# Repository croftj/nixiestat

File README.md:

# NixieStat Home Thermostat

NxieStat is thermostat for the home with a nixie tube display supporting
remote sensors.

All comminications to the thermostat is over wifi using the Mosquitto MQTT
message bus. The messages are in the form of json strings. 

This prject started out as an AVR based thermostat. You will see vestiges of
that in source tree. The latest code and hardware is under the **esp32**
folder. The hope is that there will be a web ui running on a Raspberry PI. The
start of this code is in the **webui** folder. It is very early code that is
mostly to prove certain components/SDKs such as **QT** & **WT** can actually be 
compiled together on the Rasberry PI.

## Hardware

### Devboard
This is currently the most tested of the two ESP32 boards. It handle an
ESP32-S2 processor. It also has a three pin connector for easily attaching a
DS18S20 temperature sensor to it. Its  primary purpose is for the temperature
sensors.

### Devboard2
This board is similar to *DevBoard* except that it is laid out for the
ESP32-WROVER-IE processor. This board has not been tested yet. It will
hopefully be the processor for use as the thermostat itself and be able to be
upgraded *over the air*

### CPU Board
This board has the relays for the furnace as wll as the interface chips for the
keyboard an the display board. It can use either *Devboard* or *Devboard2* for
it's processor board.

## Nixie Display
This board has the High voltage supply as well as the nixie tubes and neon
bulbs for the display.

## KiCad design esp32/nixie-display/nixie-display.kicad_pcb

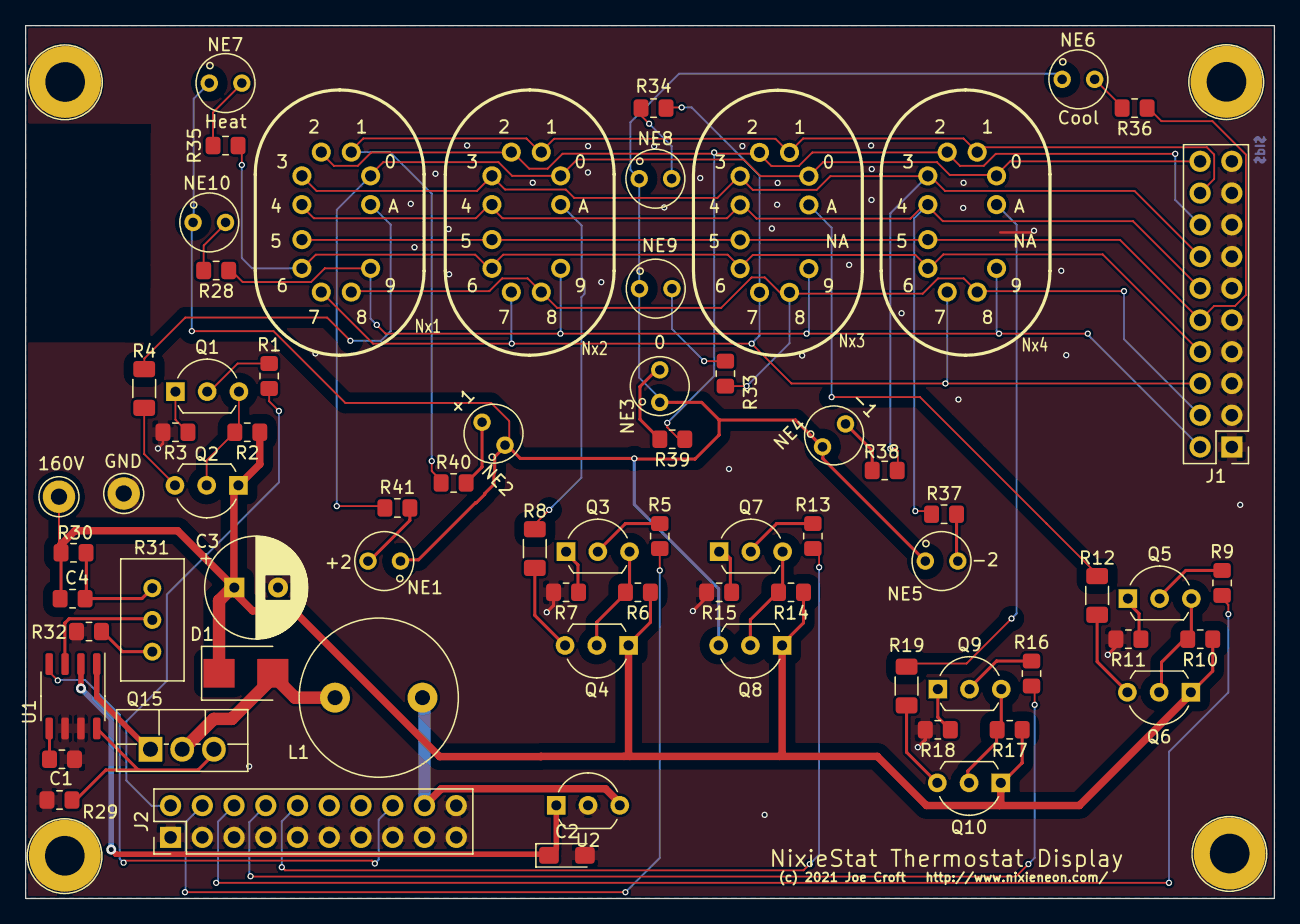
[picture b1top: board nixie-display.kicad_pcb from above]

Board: 2 copper layers, 99.9 x 69.8 mm, 74 parts (0 on the bottom side), 61 nets.

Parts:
C1: 1nf; R_0805_2012Metric_Pad1.20x1.40mm_HandSolder
C2: 10uf; CP_EIA-3216-18_Kemet-A_Pad1.58x1.35mm_HandSolder
C3: 4.7uf; CP_Radial_D8.0mm_P3.50mm
C4: 2.2nf; R_0805_2012Metric_Pad1.20x1.40mm_HandSolder
D1: D_Schottky; D_SMB
J1, J2: Conn_02x10_Odd_Even; PinHeader_2x10_P2.54mm_Vertical
L1: 150uh; L_Radial_D12.5mm_P7.00mm_Fastron_09HCP
NE1: +2; NE2
NE2: +1; NE2
NE3: 0; NE2
NE4: -1; NE2
NE5: -2; NE2
NE6: Cool; NE2
NE7: Heat; NE2
NE8, NE9, NE10: Lamp_Neon; NE2
Nx1, Nx2, Nx3, Nx4: in17
Q1, Q3, Q5, Q7, Q9: MPSA42; TO-92L_Inline_Wide
Q2, Q4, Q6, Q8, Q10: MPSA92; TO-92L_Inline_Wide
Q15: IRLS640; TO-220F-3_Vertical
R1, R3, R5, R7, R9, R11, R13, R15, R16, R18: 3.3K; R_0805_2012Metric_Pad1.20x1.40mm_HandSolder
R2, R6, R10, R14, R17, R28, R33, R34, R35, R36, R37, R38, R39, R40, R41: 100K; R_0805_2012Metric_Pad1.20x1.40mm_HandSolder
R4, R8, R12, R19: 22K; R_1206_3216Metric_Pad1.30x1.75mm_HandSolder
R29: .1; R_0805_2012Metric_Pad1.20x1.40mm_HandSolder
R30: 1M; R_0805_2012Metric_Pad1.20x1.40mm_HandSolder
R31: 20K; Potentiometer_Bourns_3296W_Vertical
R32: 1.2K; R_0805_2012Metric_Pad1.20x1.40mm_HandSolder
SH1, SH2, SH3, SH4: ScrewHole; 4-40-Screw
TP1: 160V; Pin_D1.3mm_L11.0mm
TP2: GND; Pin_D1.3mm_L11.0mm
U1: MAX1771; SO-8_3.9x4.9mm_P1.27mm
U2: L78L05_TO92; TO-92_Inline_Wide

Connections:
160V: C3.1, C4.1, D1.1, Q2.1, Q4.1, Q6.1, Q8.1, Q10.1, R2.1, R6.1, R10.1, R14.1, R17.1, R30.1, TP1.1
+5V: C2.1, U1.2, U2.1
/seg0: J1.20, Nx1.0, Nx2.0, Nx3.0, Nx4.0, R41.1
/seg1: J1.18, Nx1.1, Nx2.1, Nx3.1, Nx4.1, R40.1
/seg2: J1.16, Nx1.2, Nx2.2, Nx3.2, Nx4.2, R39.1
/seg3: J1.14, Nx1.3, Nx2.3, Nx3.3, Nx4.3, R38.1
/seg4: J1.12, Nx1.4, Nx2.4, Nx3.4, Nx4.4, R37.1
/seg5: J1.10, Nx1.5, Nx2.5, Nx3.5, Nx4.5, R36.1
/seg6: J1.8, Nx1.6, Nx2.6, Nx3.6, Nx4.6, R35.1
/seg7: J1.6, Nx1.7, Nx2.7, Nx3.7, Nx4.7, R34.1
/seg8: J1.4, Nx1.8, Nx2.8, Nx3.8, Nx4.8, R33.1
/seg9: J1.2, Nx1.9, Nx2.9, Nx3.9, Nx4.9, R28.1
GNDREF: C1.2, C2.2, C3.2, J1.1, J1.3, J1.5, J1.7, J1.9, J1.11, J1.13, J1.15, J1.17, J1.19, J2.1, J2.3, J2.5, J2.7, J2.9, J2.11, J2.13, J2.15, J2.17, J2.19, J2.20, R3.2, R7.2, R11.2, R15.2, R18.2, R29.2, R32.2, SH1.1, SH2.1, SH3.1, SH4.1, TP2.1, U1.6, U1.7, U2.2
HV_DISABLE: J2.16, U1.4
unnamed: C1.1, U1.5
unnamed: C4.2, R30.2, R31.1
unnamed: D1.2, L1.2, Q15.2
unnamed: NE1.2, R41.2
unnamed: NE2.2, R40.2
unnamed: NE3.2, R39.2
unnamed: NE4.2, R38.2
unnamed: NE5.2, R37.2
unnamed: NE6.2, R36.2
unnamed: NE7.2, R35.2
unnamed: NE8.2, R34.2
unnamed: NE9.2, R33.2
unnamed: NE10.2, R28.2
unnamed: Q1.1, R3.1
unnamed: Q1.2, R1.1
unnamed: Q1.3, Q2.2, R2.2
unnamed: Q2.3, R4.2
unnamed: Q3.1, R7.1
unnamed: Q3.2, R5.1
unnamed: Q3.3, Q4.2, R6.2
unnamed: Q4.3, R8.2
unnamed: Q5.1, R11.1
unnamed: Q5.2, R9.1
unnamed: Q5.3, Q6.2, R10.2
unnamed: Q6.3, R12.2
unnamed: Q7.1, R15.1
unnamed: Q7.2, R13.1
unnamed: Q7.3, Q8.2, R14.2
unnamed: Q9.1, R18.1
unnamed: Q9.2, R16.1
unnamed: Q9.3, Q10.2, R17.2
unnamed: Q10.3, R19.2
unnamed: Q15.1, U1.1
unnamed: Q15.3, R29.1, U1.8
unnamed: R31.2, U1.3
unnamed: R31.3, R32.1
VCC: J2.18, L1.1, U2.3
dig0: Nx1.A, R4.1
dig1: Nx2.A, R8.1
dig2: Nx3.A, R12.1
dig3: Nx4.A, R19.1
dig4: NE1.1, NE2.1, NE3.1, NE4.1, NE5.1, NE6.1, NE7.1, NE8.1, NE9.1, NE10.1, Q8.3
idig0: J2.2, R1.2
idig1: J2.4, R5.2
idig2: J2.6, R9.2
idig3: J2.8, R16.2
idig4: J2.10, R13.2

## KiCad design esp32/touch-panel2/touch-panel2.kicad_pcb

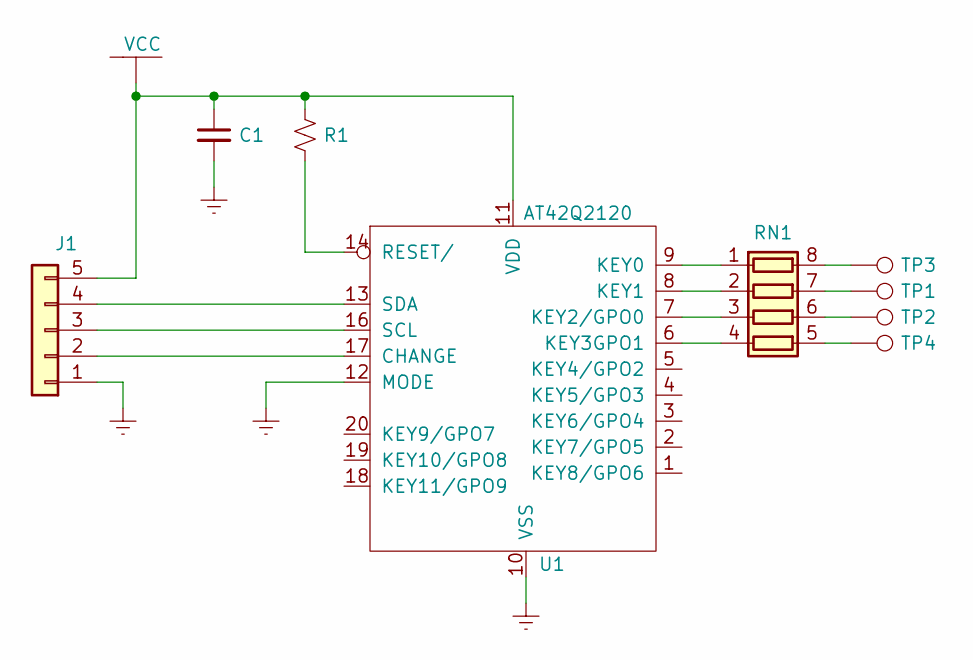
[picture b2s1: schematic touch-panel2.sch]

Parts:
C1: C_Small; C_0805_2012Metric_Pad1.18x1.45mm_HandSolder
J1: Conn_01x05; PinHeader_1x05_P2.54mm_Vertical
R1: R_Small_US; R_0805_2012Metric_Pad1.20x1.40mm_HandSolder
RN1: R_Pack04; R_Array_Convex_4x0603
TP1, TP2, TP3, TP4: TestPoint; Touch_Pad_Small
U1: AT42Q2120; TSSOP-20_4.4x6.5mm_P0.65mm
V1: VCC

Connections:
GNDREF: C1.2, J1.1, U1.10 (VSS), U1.12 (MODE)
unnamed: J1.2, U1.17 (CHANGE)
unnamed: J1.3, U1.16 (SCL)
unnamed: J1.4, U1.13 (SDA)
unnamed: R1.2, U1.14 (RESET/)
unnamed: RN1.1 (R1.1), U1.9 (KEY0)
unnamed: RN1.2 (R2.1), U1.8 (KEY1)
unnamed: RN1.3 (R3.1), U1.7 (KEY2/GPO0)
unnamed: RN1.4 (R4.1), U1.6 (KEY3GPO1)
unnamed: RN1.5 (R4.2), TP4.1
unnamed: RN1.6 (R3.2), TP2.1
unnamed: RN1.7 (R2.2), TP1.1
unnamed: RN1.8 (R1.2), TP3.1
VCC: C1.1, J1.5, R1.1, U1.11 (VDD), V1.1

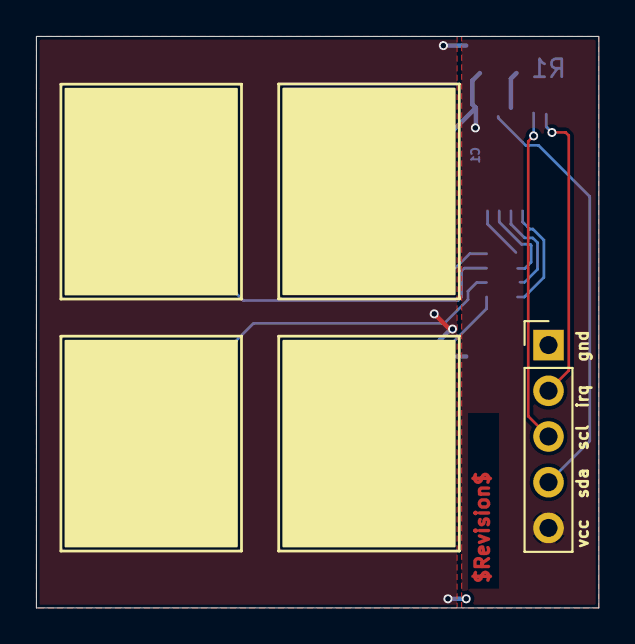
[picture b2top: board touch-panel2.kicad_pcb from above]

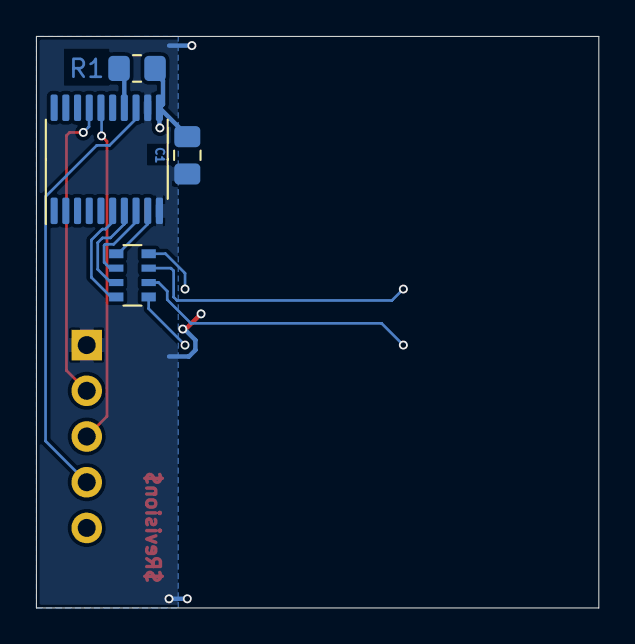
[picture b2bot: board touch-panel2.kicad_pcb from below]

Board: 2 copper layers, 31.2 x 31.7 mm, 9 parts (4 on the bottom side), 14 nets.

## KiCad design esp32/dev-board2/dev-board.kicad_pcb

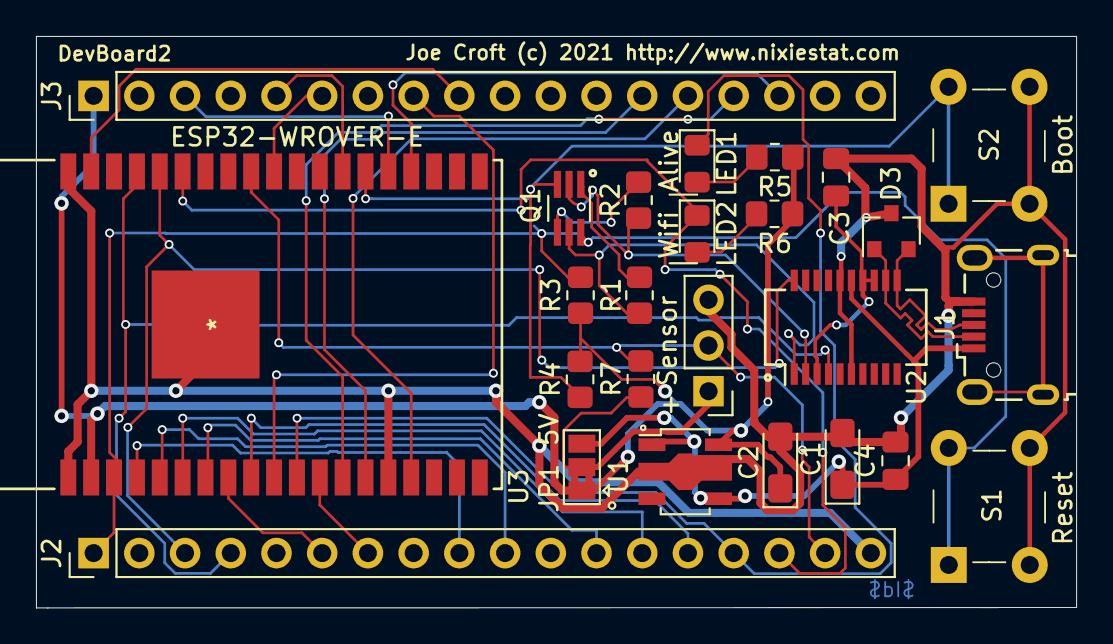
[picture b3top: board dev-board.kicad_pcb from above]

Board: 2 copper layers, 57.8 x 31.8 mm, 25 parts (0 on the bottom side), 36 nets.

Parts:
C1, C2: 10uf; CP_EIA-3216-18_Kemet-A_Pad1.58x1.35mm_HandSolder
C3, C4: .1uf; C_0805_2012Metric_Pad1.18x1.45mm_HandSolder
D3: STS232; SOT-23
J1: USB_B_Micro; USB_Micro-B_Wuerth_629105150521
J2, J3: Conn_01x18_Male; PinHeader_1x18_P2.54mm_Vertical
J4: Conn_01x03_Male; PinHeader_1x03_P2.54mm_Vertical
JP1: Jumper_3_Bridged12; SolderJumper-3_P1.3mm_Bridged2Bar12_Pad1.0x1.5mm
LED1, LED2: LED; LED_0805_2012Metric_Pad1.15x1.40mm_HandSolder
Q1: MTB3904-2; SOT-363_SC-70-6_Handsoldering
R1, R2, R3, R4: 10K; R_0805_2012Metric_Pad1.20x1.40mm_HandSolder
R5, R6: 75; R_0805_2012Metric_Pad1.20x1.40mm_HandSolder
R7: 2.3K; R_0805_2012Metric_Pad1.20x1.40mm_HandSolder
S1, S2: B3F-1052; Switch_Tactile_THT_B3F-1xxx
U1: AP7361C-33Y5-13; SOT-89-5
U2: FT231XS; SSOP-20_3.9x8.7mm_P0.635mm
U3: ESP32-WROVER-E; ESP32-WROVER-EM213EH2864PH3Q0

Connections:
+3.3V: C2.1, J3.1, JP1.1, R3.2, R4.2, R5.1, R6.1, U1.5, U3.2
+5V: C1.1, C4.1, J1.1, JP1.3, U1.1, U1.4, U2.15
/USB_N: D3.1, J1.2, U2.12
/USB_P: D3.2, J1.3, U2.11
GNDREF: C1.2, C2.2, C3.2, C4.2, D3.3, J1.5, J2.18, J4.3, S1.3, S1.4, S2.3, S2.4, U1.2, U2.6, U2.16, U3.1, U3.15, U3.38, U3.39
IO-00: Q1.3, R4.1, S2.1, S2.2, U3.25
IO-02: J3.3, U3.24
IO-04: J3.5, U3.26
IO-05: J3.6, U3.29
IO-12: J3.13, U3.14
IO-13: J3.14, U3.16
IO-14: J3.15, U3.13
IO-15: J3.16, U3.23
IO-18: J2.17, J4.2, R7.2, U3.30
IO-21: J2.16, LED2.1, U3.33
IO-23: J3.9, U3.37
IO-25: J3.8, U3.10
IO-26: J2.15, LED1.1, U3.11
IO-27: J2.7, U3.12
IO-32: J2.6, U3.8
IO-33: J2.14, U3.9
IO-34: J2.13, U3.6
IO-35: J2.12, U3.7
unnamed: C3.1, U2.3, U2.13, U2.14
unnamed: J4.1, JP1.2, R7.1
unnamed: LED1.2, R5.2
unnamed: LED2.2, R6.2
unnamed: Q1.1, R1.2
unnamed: Q1.2, R2.1, U2.2
unnamed: Q1.4, R2.2
unnamed: Q1.5, R1.1, U2.1
RESET: J2.1, Q1.6, R3.1, S1.1, S1.2, U3.3
RXD0: J2.3, U2.20, U3.34
SENSOR_VN: J2.10, U3.5
SENSOR_VP: J2.9, U3.4
TXD0: J2.4, U2.4, U3.35

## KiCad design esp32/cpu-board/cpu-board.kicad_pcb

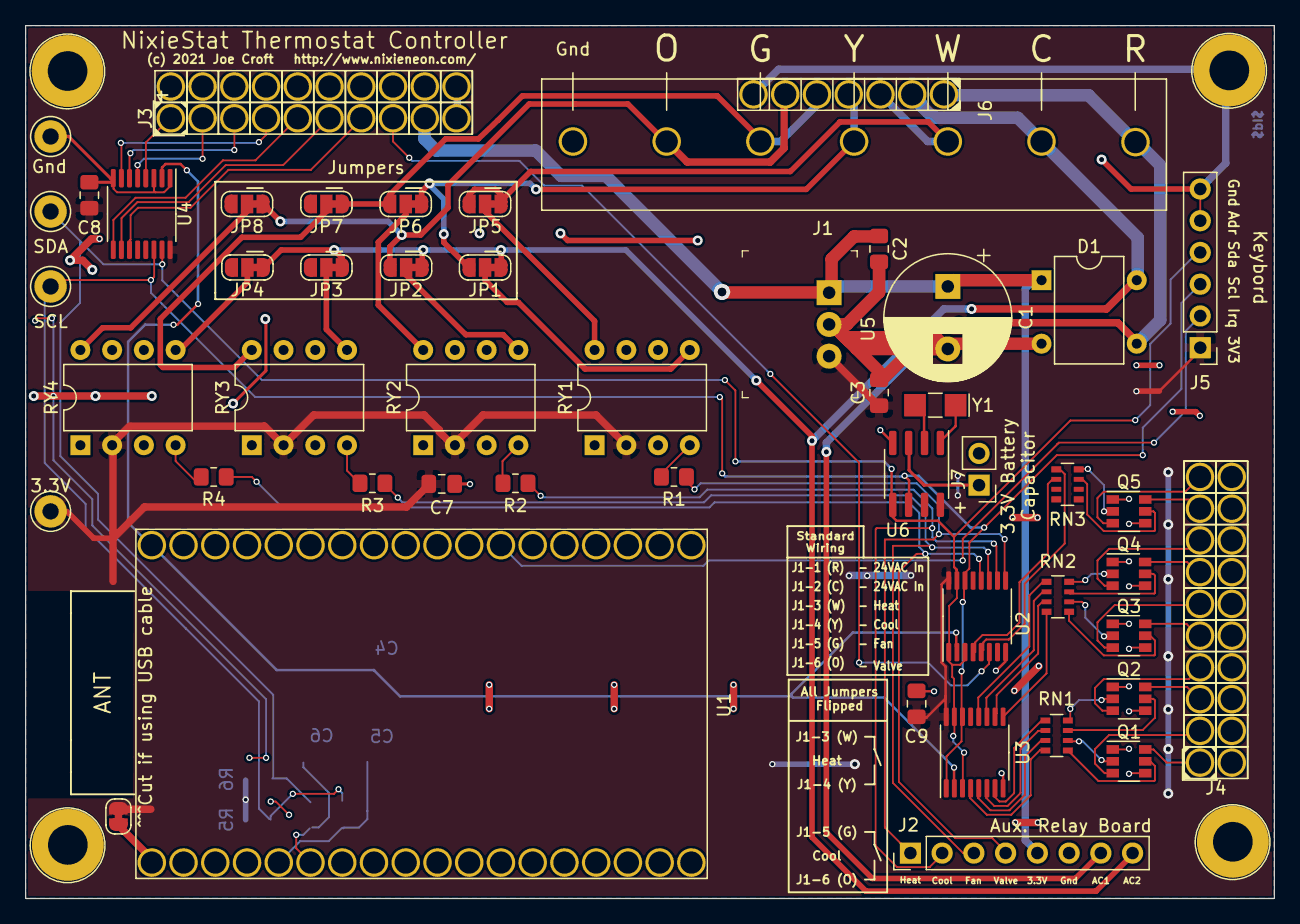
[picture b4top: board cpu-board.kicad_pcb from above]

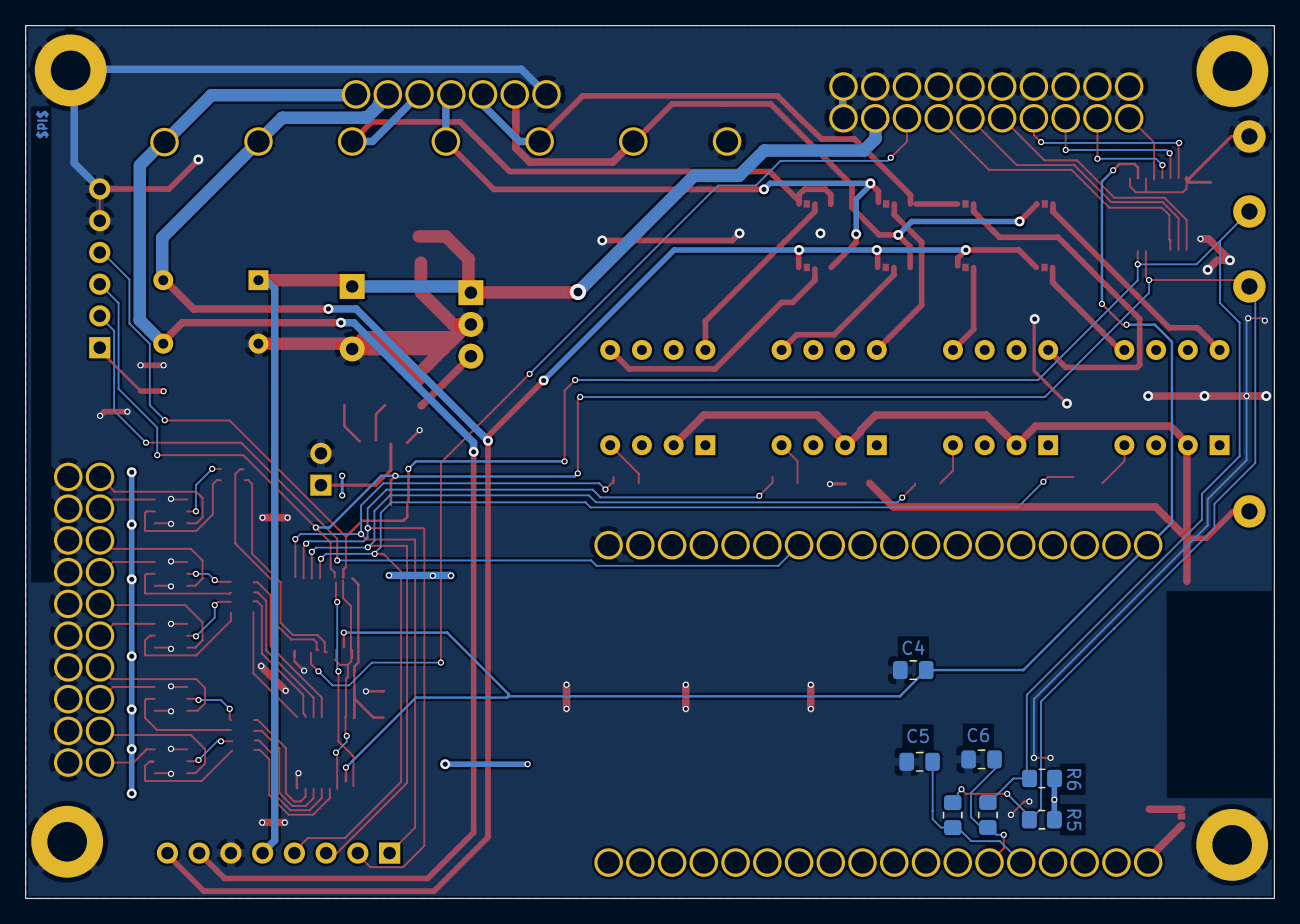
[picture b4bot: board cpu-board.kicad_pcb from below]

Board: 2 copper layers, 99.9 x 69.8 mm, 61 parts (7 on the bottom side), 73 nets.

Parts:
C1: 100uf 35V; CP_Radial_D10.0mm_P5.00mm
C2, C3: 10uf 35V; C_0805_2012Metric_Pad1.18x1.45mm_HandSolder
C4, C5, C6, C7, C8, C9: .1uf; C_0805_2012Metric_Pad1.18x1.45mm_HandSolder
D1: DF01M; Diode_Bridge_DIP-4_W7.62mm_P5.08mm
J1: Conn_01x07; conn-phx-1703090
J2: Conn_01x08; PinHeader_1x08_P2.54mm_Vertical
J3: Conn_02x10_Odd_Even; pcb_jack-2x10
J4: Conn_02x10_Odd_Even; pcb_jack-2x10-mirror
J5: Conn_01x06; PinHeader_1x06_P2.54mm_Vertical
J6: Conn_01x07; Mill-Max-295x7
J7: Battery; PinHeader_1x02_P2.54mm_Vertical
JP1, JP2, JP3, JP4, JP5, JP6, JP7, JP8: SolderJumper_3_Bridged12; SolderJumper-3_P1.3mm_Bridged12_RoundedPad1.0x1.5mm_NumberL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
JP9: Jumper_2_Bridged; SolderJumper-2_P1.3mm_Bridged_RoundedPad1.0x1.5mm
Q1, Q2, Q3, Q4, Q5: PMBTA42DS,125; SuperSOT-6
R1, R2, R3, R4: R_US; R_0805_2012Metric_Pad1.20x1.40mm_HandSolder
R5, R6: 100K; R_0805_2012Metric_Pad1.20x1.40mm_HandSolder
R7, R8: 0 Ohm; R_0805_2012Metric_Pad1.20x1.40mm_HandSolder
RN1, RN2, RN3: R_Pack04; R_Array_Convex_4x0603
RY1, RY2, RY3, RY4: AQH3213; DIP-8_W7.62mm
SH1, SH2, SH3, SH4: ScrewHole; 4-40-Screw
TP1: Gnd; Pin_D1.3mm_L11.0mm
TP2: SCL; Pin_D1.3mm_L11.0mm
TP3: SDA; Pin_D1.3mm_L11.0mm
TP4: 3.3V; Pin_D1.3mm_L11.0mm
U1: ESP32-DevBoard2; ESP32-DevKit-pcb-recepticals
U2, U3, U4: MAX7320; TSSOP-16_4.4x5mm_P0.65mm
U5: V7803-1000; 3-SIP_Module_V7805-1000
U6: PT7C4339; SOIC-8_3.9x4.9mm_P1.27mm
Y1: 32.788Khz; Crystal_SMD_G8-2Pin_3.2x1.5mm_HandSoldering

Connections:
+3.3V: C3.1, C7.1, C8.1, C9.1, J5.1, JP9.1, R5.1, R6.1, RY1.2, RY2.2, RY3.2, RY4.2, TP4.1, U2.16, U3.16, U4.16, U5.3, U6.8
AC1: D1.3, J1.1, J2.7, J6.1
AC2: D1.4, J1.2, J2.8, J6.2, JP1.1, JP2.1, JP3.1, JP4.1
COOL: J2.2, R2.2, U2.10
FAN: J2.3, R3.2, U2.11
GNDREF: C1.2, C2.2, C3.2, C4.2, C5.2, C6.2, C7.2, C8.2, C9.2, D1.2, J1.7, J2.6, J3.2, J3.4, J3.6, J3.8, J3.10, J3.12, J3.14, J3.16, J3.18, J3.19, J3.20, J4.2, J4.4, J4.6, J4.8, J4.10, J4.12, J4.14, J4.16, J4.18, J4.20, J5.5, J5.6, J6.7, J7.2, Q1.1, Q1.4, Q2.1, Q2.4, Q3.1, Q3.4, Q4.1, Q4.4, Q5.1, Q5.4, SH1.1, SH2.1, SH3.1, SH4.1, TP1.1, U1.19, U2.8, U3.8, U4.1, U4.3, U4.8, U5.2, U6.4
HEAT: J2.1, R1.2, U2.9
I2C_SCL: J5.3, R5.2, R7.1, TP2.1, U2.14, U3.1, U3.14, U4.14, U6.6
I2C_SDA: J5.4, R6.2, R8.1, TP3.1, U2.1, U2.3, U2.15, U3.3, U3.15, U4.15, U6.5
KEY_IRQ: J5.2, U1.25
unnamed: C5.1, R7.2, U1.5
unnamed: C6.1, R8.2, U1.6
unnamed: J1.3, J6.3, JP5.1, JP5.3
unnamed: J1.4, J6.4, JP1.3, JP6.1
unnamed: J1.5, J6.5, JP6.3, JP7.1
unnamed: J1.6, J6.6, JP2.3, JP8.1
unnamed: J3.1, U4.4
unnamed: J3.3, U4.5
unnamed: J3.5, U4.6
unnamed: J3.7, U4.7
unnamed: J3.9, U4.9
unnamed: J3.11, U4.10
unnamed: J3.13, U4.11
unnamed: J7.1, U6.3
unnamed: JP1.2, RY1.5
unnamed: JP2.2, RY2.5
unnamed: JP3.2, RY3.5
unnamed: JP4.2, RY4.5
unnamed: JP5.2, RY1.8
unnamed: JP6.2, RY2.8
unnamed: JP7.2, RY3.8
unnamed: JP8.2, RY4.8
unnamed: JP9.2, U1.1
unnamed: R1.1, RY1.4
unnamed: R2.1, RY2.4
unnamed: R3.1, RY3.4
unnamed: R4.1, RY4.4
unnamed: RN1.5, U3.7
unnamed: RN1.6, U3.6
unnamed: RN1.7, U3.5
unnamed: RN1.8, U3.4
unnamed: RN2.5, U3.12
unnamed: RN2.6, U3.11
unnamed: RN2.7, U3.10
unnamed: RN2.8, U3.9
unnamed: RN3.5, U2.5
unnamed: RN3.6, U2.4
unnamed: U6.1, Y1.1
unnamed: U6.2, Y1.2
RESET: C4.1, U1.36, U2.2, U3.2, U4.2
SEG1: Q1.5, RN1.1
SEG2: Q1.2, RN1.2
SEG3: Q2.5, RN1.3
SEG4: Q2.2, RN1.4
SEG5: Q3.5, RN2.1
SEG6: Q3.2, RN2.2
SEG7: Q4.5, RN2.3
SEG8: Q4.2, RN2.4
SEG9: Q5.5, RN3.3
SEG10: Q5.2, RN3.4
SEG_D_1: J4.1, Q1.6
SEG_D_2: J4.3, Q1.3
SEG_D_3: J4.5, Q2.6
SEG_D_4: J4.7, Q2.3
SEG_D_5: J4.9, Q3.6
SEG_D_6: J4.11, Q3.3
SEG_D_7: J4.13, Q4.6
SEG_D_8: J4.15, Q4.3
SEG_D_9: J4.17, Q5.6
SEG_D_10: J4.19, Q5.3
VALVE: J2.4, R4.2, U2.12
VCC: C1.1, C2.1, D1.1, J2.5, J3.17, U5.1
~HV_EN~: J3.15, U2.6

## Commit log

2022-01-16 Initial import of //depot/nixiestat/ from the state at revision #head
    [git-p4: depot-paths = "//depot/nixiestat/": change = 313]
2022-01-16 Initial revision for the display pcb and schematic
    [git-p4: depot-paths = "//depot/nixiestat/": change = 315]
2022-01-16 Added ground connection, broke the schematic into two sheets
    [git-p4: depot-paths = "//depot/nixiestat/": change = 316]
2022-01-17 Set the default logging level to 'Warning'
    [git-p4: depot-paths = "//depot/nixiestat/": change = 318]
2022-01-17 Added README file
    [git-p4: depot-paths = "//depot/nixiestat/": change = 319]
2022-01-31 Fixed IN-17 foot prints, Anode drivers, little stuff
    [git-p4: depot-paths = "//depot/nixiestat/": change = 320]
2022-01-31 Bumped the revision to match the other files
    [git-p4: depot-paths = "//depot/nixiestat/": change = 321]
2022-02-04 Modified to to use simplified keys through the json interface Modified to provide feedback on invalid keys Added seperate json discovery commands show_keys, known_sensors
    [git-p4: depot-paths = "//depot/nixiestat/": change = 323]
2022-02-25 First attempt at ensuring proper grounding Added capacitor to the reset pin Extended the reset line to the IO extenders
    [git-p4: depot-paths = "//depot/nixiestat/": change = 324]
2022-02-25 Moved the text on the bottom silkscreen to the bottom copper
    [git-p4: depot-paths = "//depot/nixiestat/": change = 325]
2022-02-25 Updated fill zones
    [git-p4: depot-paths = "//depot/nixiestat/": change = 326]
2022-02-25 Just a small fix
    [git-p4: depot-paths = "//depot/nixiestat/": change = 327]
2022-02-25 Improved grounding New Anode Drivers
    [git-p4: depot-paths = "//depot/nixiestat/": change = 328]
2022-02-25 Small change
    [git-p4: depot-paths = "//depot/nixiestat/": change = 329]
2022-02-27 Finishing touches on the board clean up (until the next round)
    [git-p4: depot-paths = "//depot/nixiestat/": change = 330]
2022-02-27 Design Rule cleanup
    [git-p4: depot-paths = "//depot/nixiestat/": change = 331]
2022-02-28 Further ground work
    [git-p4: depot-paths = "//depot/nixiestat/": change = 332]
2022-02-28 Further ground work
    [git-p4: depot-paths = "//depot/nixiestat/": change = 333]
2022-03-02 Fixed SensorData::isValid, Added multi-sensor target support
    [git-p4: depot-paths = "//depot/nixiestat/": change = 334]
2022-03-17 Added RTC
    [git-p4: depot-paths = "//depot/nixiestat/": change = 335]
2022-03-31 Changed RTOS tick to 1ms, restructured wifi processing, added display and keyboard handling, integrated PT7C4339 RTC into the code
    [git-p4: depot-paths = "//depot/nixiestat/": change = 336]
2022-03-31 Cleaned up most warnings
    [git-p4: depot-paths = "//depot/nixiestat/": change = 337]
2022-05-29 New Zen design
    [git-p4: depot-paths = "//depot/nixiestat/": change = 356]
2022-05-29 Added new 4 key touch pad board
    [git-p4: depot-paths = "//depot/nixiestat/": change = 357]
2022-05-29 Fixed keywords for PCB
    [git-p4: depot-paths = "//depot/nixiestat/": change = 358]
2022-05-29 Fixed copper zone
    [git-p4: depot-paths = "//depot/nixiestat/": change = 359]
2022-05-29 Updated dates and such
    [git-p4: depot-paths = "//depot/nixiestat/": change = 360]
2022-07-12 Added RTC functionality, modified the display to be more Zen
    [git-p4: depot-paths = "//depot/nixiestat/": change = 366]

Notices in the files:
esp32/cpu-board/cpu-board.kicad_pcb:
(c) 2021 Joe Croft http://www.nixieneon.com
esp32/dev-board2/dev-board.kicad_pcb:
Joe Croft (c) 2021 http://www.nixiestat.com
parts and their libraries:
Copyright 2016 Accelerated Designs. All rights reserved.
